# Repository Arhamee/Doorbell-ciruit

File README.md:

# Doorbell-ciruit
Its an door bell circuit 
This project demonstrates a simple doorbell circuit built around the classic NE555 timer IC. When the push button is pressed, the 555 timer generates a clear ~2kHz audible tone through an speaker, functioning as an effective door alert system

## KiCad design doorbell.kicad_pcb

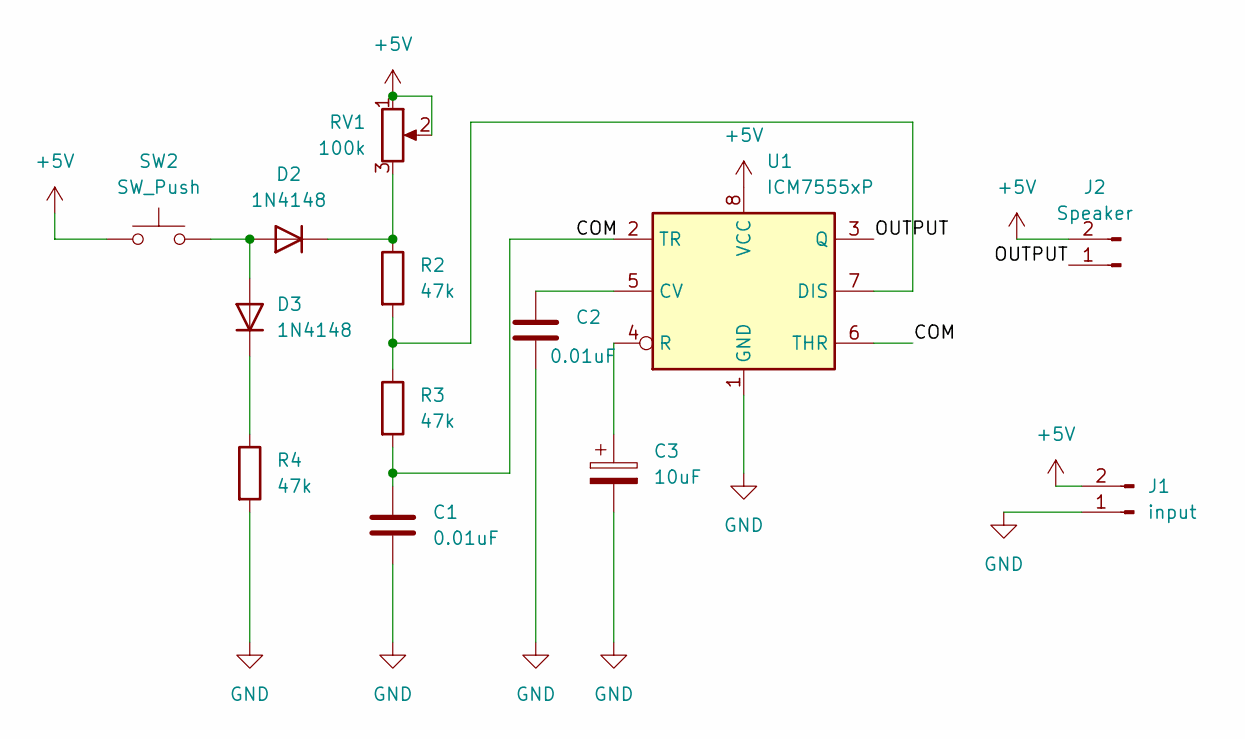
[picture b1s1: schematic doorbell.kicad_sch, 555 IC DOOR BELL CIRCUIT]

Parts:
C1, C2: 0.01uF; CP_Radial_D4.0mm_P2.00mm
C3: 10uF; CP_Radial_D5.0mm_P2.00mm
D2, D3: 1N4148; D_DO-35_SOD27_P7.62mm_Horizontal
J1: input; TerminalBlock_MaiXu_MX126-5.0-02P_1x02_P5.00mm
J2: Speaker; TerminalBlock_MaiXu_MX126-5.0-02P_1x02_P5.00mm
R2, R3, R4: 47k; R_Axial_DIN0207_L6.3mm_D2.5mm_P10.16mm_Horizontal
RV1: 100k; Potentiometer_Bourns_3296W_Vertical
SW2: SW_Push; SW_DIP_SPSTx01_Piano_10.8x4.1mm_W7.62mm_P2.54mm
U1: ICM7555xP; DIP-8_W7.62mm

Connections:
+5V: J1.2, J2.2, RV1.1, RV1.2, SW2.1, U1.8 (VCC)
/COM: C1.1, R3.2, U1.2 (TR), U1.6 (THR)
/OUTPUT: J2.1, U1.3 (Q)
GND: C1.2, C2.2, C3.2, J1.1, R4.2, U1.1 (GND)
unnamed: D2.2 (A), D3.2 (A), SW2.2
unnamed: D2.1 (K), R2.1, RV1.3
unnamed: D3.1 (K), R4.1
unnamed: C2.1, U1.5 (CV)
unnamed: R2.2, R3.1, U1.7 (DIS)
unnamed: C3.1, U1.4 (R)

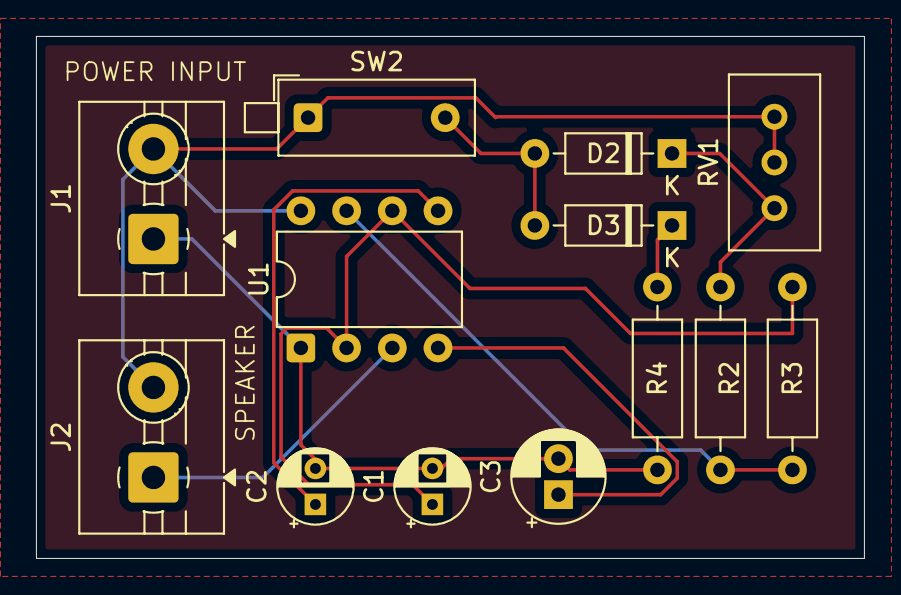
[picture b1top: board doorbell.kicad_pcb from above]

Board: 2 copper layers, 46.0 x 29.0 mm, 13 parts (0 on the bottom side), 10 nets.
